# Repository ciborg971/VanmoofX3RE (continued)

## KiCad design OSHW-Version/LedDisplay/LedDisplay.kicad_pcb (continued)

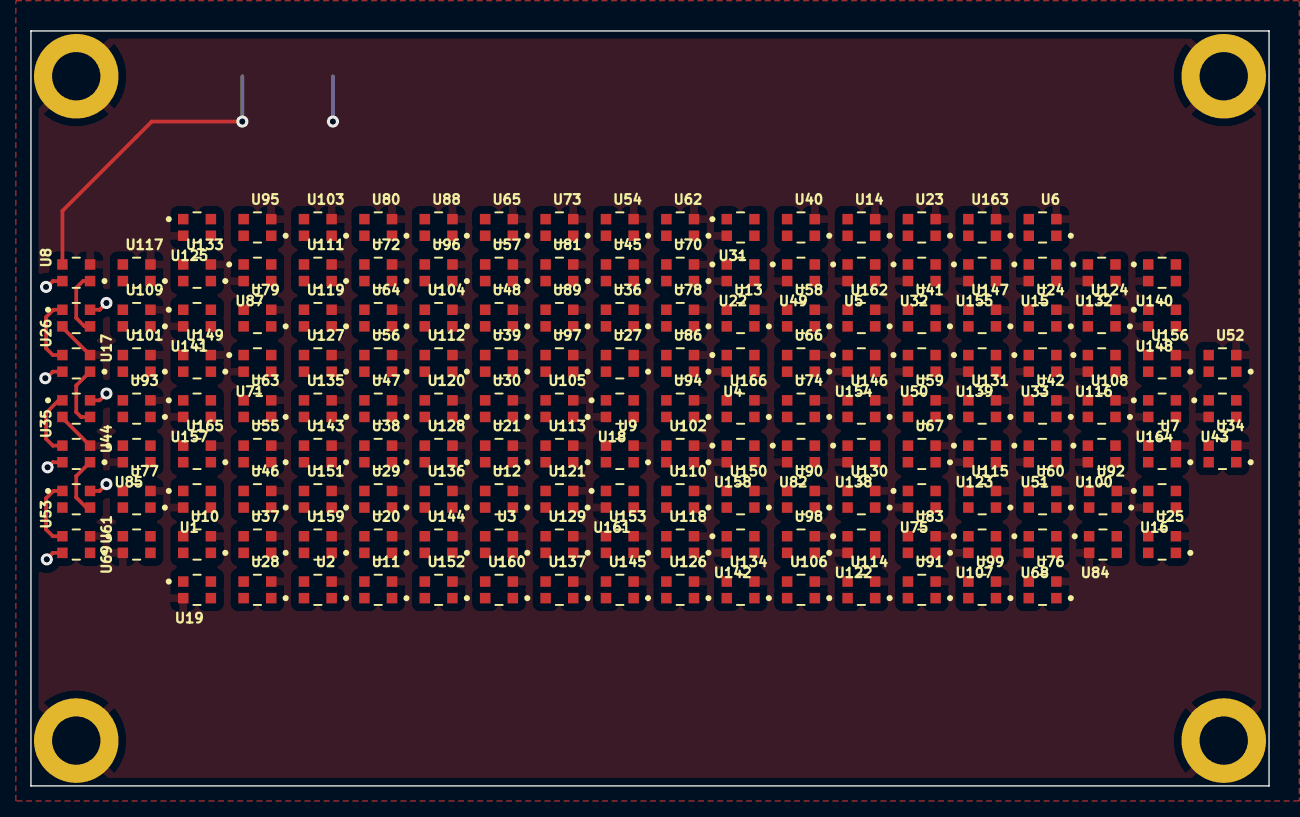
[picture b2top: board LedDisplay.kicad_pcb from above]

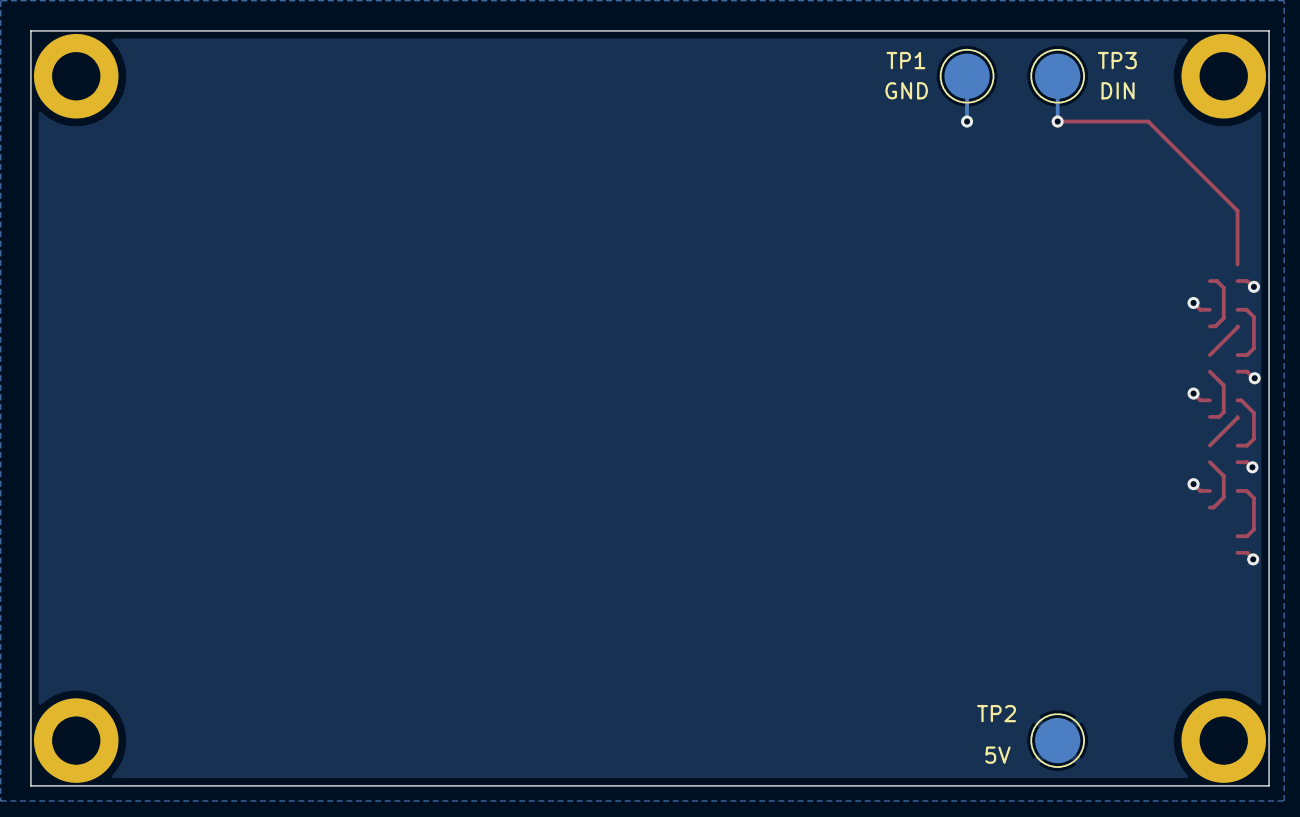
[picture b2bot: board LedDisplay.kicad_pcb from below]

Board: 2 copper layers, 82.0 x 50.0 mm, 173 parts (3 on the bottom side), 168 nets.

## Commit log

2023-08-11 basic component listing for the original boards
2023-08-11 mainboard pictures
2023-08-13 start smart cartridge housing + kicad project
2023-08-15 bms pictures + info
2023-08-15 bms kicad project with board outline
2023-08-15 SmartCartridge Kicad : brushless, battery connector and button placement
    + spotted all the ground
2023-08-15 readme refacto, add datasheet, add led display, progress smartcartridge
2023-08-16 more information about bms
2024-04-02 display flex scans
